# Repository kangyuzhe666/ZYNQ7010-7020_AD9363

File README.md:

# ZYNQ7010/7020_AD9363/AD9364/AD9361

####  Open source SDR hardware based on ZYNQ+AD936X

[中文](./README_CN.md) 
##  Open source SDR hardware based on ZYNQ+AD936X

## The preliminary development work has been completed and the product has entered the trial production stage. Please contact the email address: 1399109998@qq.com for finished products.
2022-09-13 update

## formal support openwifi

openwifi test video
- https://www.bilibili.com/video/BV1hB4y1k7dm?spm_id_from=333.999.list.card_archive.click

Project introduction video:

- https://www.youtube.com/watch?v=Qk-M8yRsKvs 

- https://www.youtube.com/watch?v=xx4MXQSHmCM&t=153s

GSM signals receiver test:
- https://www.youtube.com/watch?v=yFEpSrWW0-w

FM signal receiver test:
- https://www.youtube.com/watch?v=ASb7dLIEmfY

Sine wave signal transmission test:
- https://www.youtube.com/watch?v=bfs_GfULIoA&t=55s

Loopback signal test:
- https://www.youtube.com/watch?v=JOjsKboq0xA

The pluto-sdr firmware transplantation work is all done, flashing the firmware without hacking the system, the default is AD9364.

#### 1. Hardware solution

FPGA: ZYNQ7010/7020 (ZYNQ7010 and ZYNQ7020 can be replaced with each other, if you need more hardware resources, please use ZYNQ7020)

RF: AD9361/AD9363/AD9364 (the three chips can be replaced with each other, the difference lies in the bandwidth. Among them, AD9361 has better performance, try to use the ABCZ ending chip, which is different from BBCZ)

https://ez.analog.com/wide-band-rf-transceivers/design-support/f/q-a/80027/what-is-difference-of-ad9363-abcz-and-bbcz?ReplyOffsetId=179002&ReplyOffsetDirection=Next&ReplySortBy=CreatedDate&ReplySortOrder=Ascending&pifragment-7309=2

AD9363ABCZ Band: 325 MHz to 3.8 GHz

AD9363BBCZ Band: 650 MHz to 2.7 GHz

RAM Memory: DDR3 256M16

USB-PHY: USB3320C

GMAC-PHY: RTL8211E-VL (RTL8211E has two endings, VB and VL, where VB level is 3.3V/2.5V, VL is 1.8V)

QSPI FLASH: W25Q256 32MB

Power supply topology diagram

block design

##### 2. Software resources

Support Pluto-SDR firmware transplantation, OpenWiFi (ZYNQ7020 FPGA required), support adi official ZED+AD-FMCOMMS2/3/4 related firmware code

#### 3. PCB board design

Design software:  Altium Designer Kicad

Number of layers: 4 layers （signal layer[1]、GND[2]、POWER[3]、signal layer[4]）

Craft: JLC PCB Craft

Impedance: not supported

The impedance version will be tested in March 2021, and the openwifi port is currently undergoing normal transceiver tests.

#### 4. Differences compared to ADALM-PLUTO:

- Support for Zynq-7020 and Zynq-7010 in 400pin BGA package
- Support 2R2T transceiver mode
- 4 layer board to reduce cost
- SD slot for running real Linux distros
- Support Gigabit Ethernet

#### 5. Project display:

This is the PCB rendering

This is the physical picture of the PCB

This is the details of the PCB RF part

Ethernet can work stably at 1000M (using single-arm routing for testing in the figure)

AD9363 initializes the normal graph using adi no-os test environment

Pluto-uboot transplanted successfully

Pluto firmware works fine

Receive GSM signal normally

Hack into AD9364 to receive FM signal

Two PCBAs receive and send each other test

PCBAs can be stacked on each other and connected through Gigabit switches and routers

Support SDR-SHARP

##### 6.TO DO LIST

- Continue to optimize the RF part to reach the adi official demo board indicators
- Impedance design based on four-layer pcb
- To be completed in January-February of 2021, to complete the relevant transplantation work of openwifi
- Design the impedance version in March 2021
- Conduct commercial index tests on the impedance version in April 2021
- When the commercial version is launched at the end of April 2021, it will support adi's official SDR firmware (ADRV9364 packet), openwifi, and openbts openbts, etc.

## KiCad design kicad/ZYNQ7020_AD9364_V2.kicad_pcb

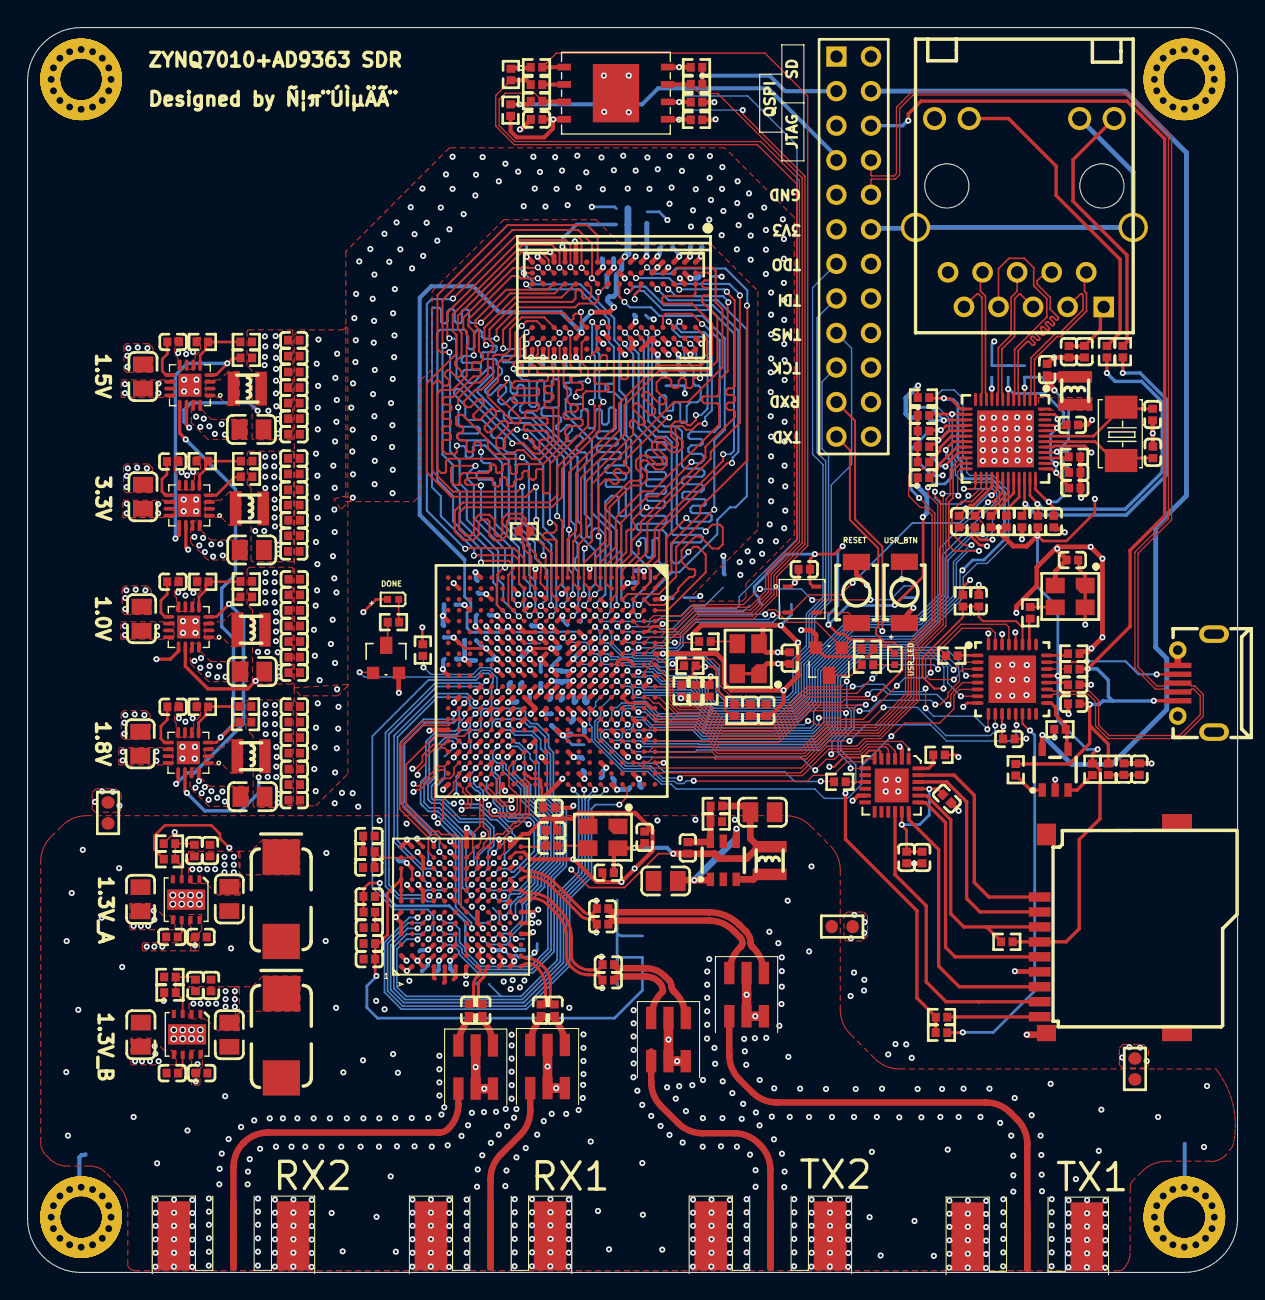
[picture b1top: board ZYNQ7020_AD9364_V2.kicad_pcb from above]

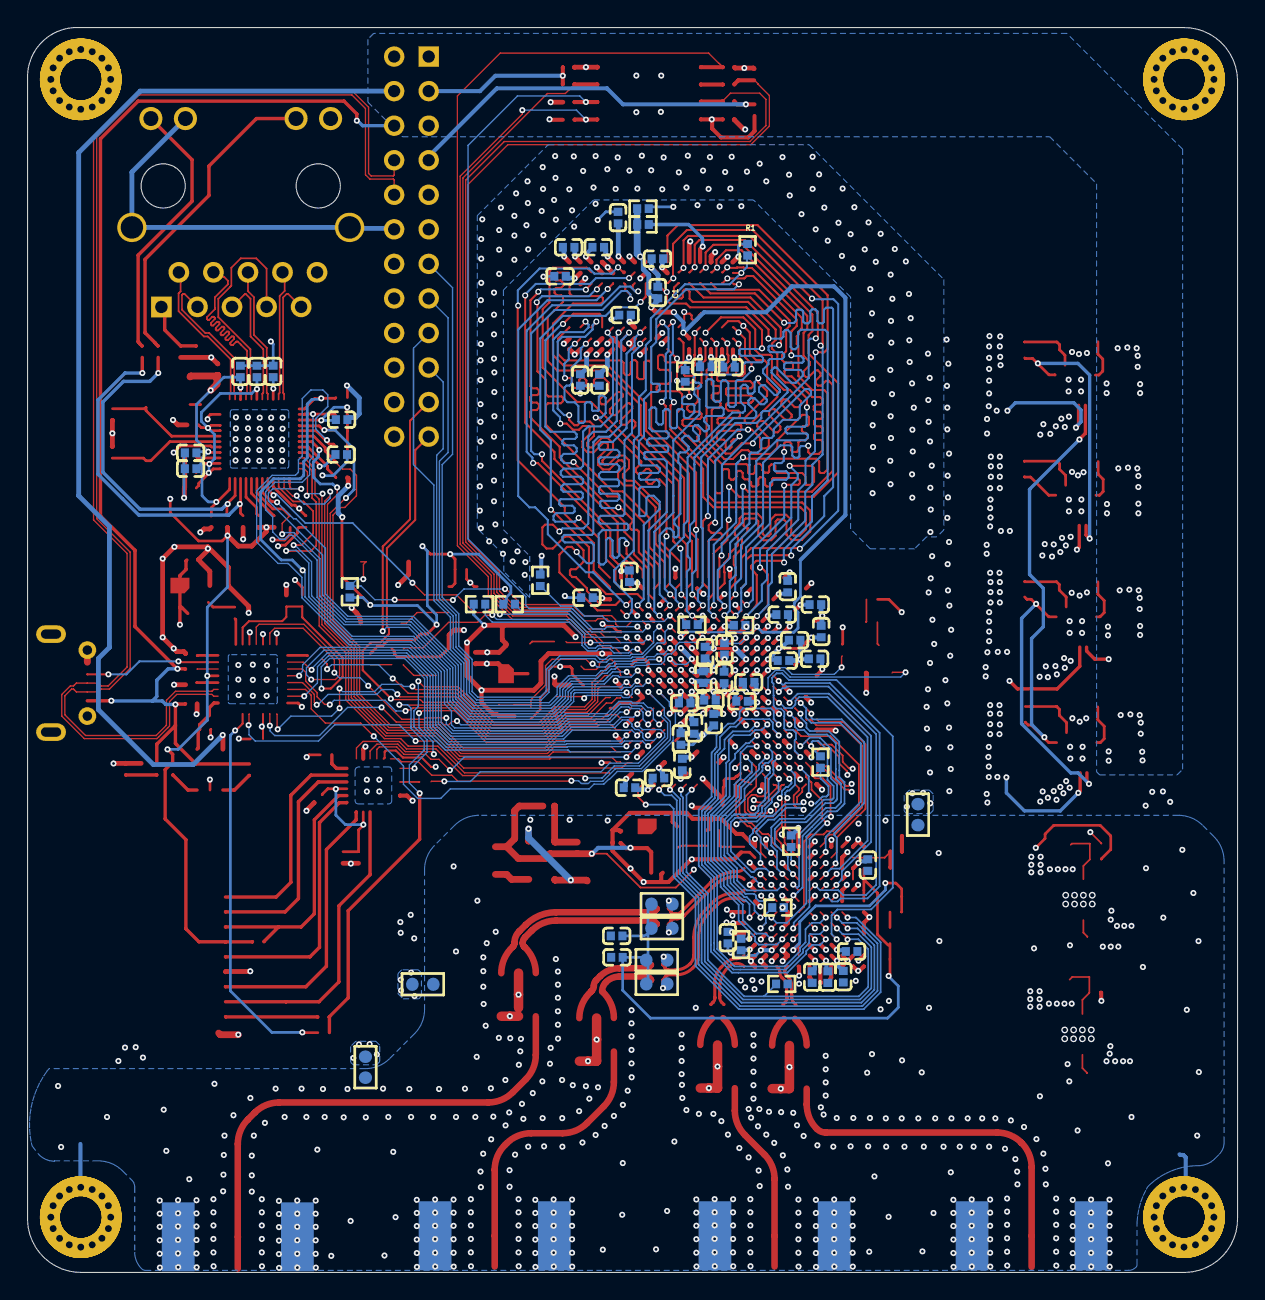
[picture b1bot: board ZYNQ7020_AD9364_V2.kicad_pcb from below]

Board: 4 copper layers, 89.0 x 91.5 mm, 287 parts (71 on the bottom side), 278 nets.

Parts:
*: W25Q128
C1, C159, C160, C161, C187, C188, C189, C190, C191, C192, C193: 104; CAP
C2, C3, C4, C5, C8, C9, C10, C12, C33, C34, C35, C36, C37, C38, C39, C49, C50, C51, C52, C53, C57, C61, C62, C67, C68, C69, C70, C71, C72, C73, C74, C75, C76, C77, C78, C80, C81, C82, C83, C85, C86, C87, C89, C90, C91, C96, C98, C99, C100, C101, C102, C103, C104, C105, C106, C107, C108, C148, C149, C181, C182, C183: 10¦ÌF; CAP_3
C6, C7, C11, C13, C18, C21, C23, C26, C27, C28: 0.1¦ÌF; CAP_3
C16, C29, C30, C31, C32, C40, C47, C48, C117, C118, C150, C152: 18p; CAP_1
C17, C20, C22, C25: 2.2¦ÌF; CAP_3
C19, C24: 3.3nF; CAP_3
C58, C60, C121, C139, C144: 10¦Ì; CAP_2
C59, C63: 0.001¦Ì; CAP_2
C109, C110, C111, C113, C114, C115, C116, C124, C125, C126, C127, C128, C130, C131, C142: 1¦Ì; CAP_2
C112, C120, C122, C132, C133, C134, C138, C141, C143: 0.1¦Ì; CAP_2
C119: 0.01¦Ì; CAP_2
C129, C135, C136, C137: 4.7¦Ì; CAP_2
C145, C166, C170, C172, C174: 1¦Ì; CAP_1
C146, C151, C175, C177: 0.001¦Ì; CAP_1
CP1, CP3: 22uF; CAP_1
CP2: 22pF; CAP_2
Ct1, Ct2: 3.3nF; CAP_3_3
DONE: LED; LED0
J2: microusb
L1, L2, L3, L4, L6: 2.2uH; INDUCTANCE_1
L5, L7, L8, L9: 330nh; INDUCTANCE
LG1: HR911130C
LP1: 4.7uH; INDUCTANCE
P2: Header 12X2A
Q1, Q2: AO3400
R1, R4, R5, R27, R35, R36, R38, R39, R40, R41, R43, R45, R46, R55, R57, R62, R63: 4.7K; RES
R2, R3: 82R; RES
R6: 240R; RES
R7, R68: 100K; RES
R8, R13, R15, R19, R24, R25, R30, R54, R65, R69, R71: 10K; RES
R9: 4.99K; RES
R10: 18.7K; RES
R11, R47, R49, R50, R51, R52, R53, R56: 20K; RES
R12, R17: 15K; RES
R14: 13K; RES
R16: 56.2K; RES
R18: 18K; RES
R20: 80.6R; RES
R21, R22: 6.25K; RES
R23, R64, R67: 0R; RES
R26: 2.49K; RES
R28, R29, R37, R42, R58, R76: 33R; RES
R31, R32, R70: 330R; RES
R33, R34: 1.5K; RES
R44: 8.06K; RES
R48, R66: 1K; RES
R59, R60, R61: 470R; RES
R72: 40.2R; RES
R73, R74: 1R; RES_1
R75: 14.3K; RES_1
RESET: SW-PB
RP1: 10K; RES_1
RP2: 20K; RES_1
RX1, RX2: JCCEM001
RX4, RX5, RX6, RX7, RX8, RX10, RX13, RX14, RX15, RX22: 0R; RES_1
T1, T2, T3, T4: TCM1-63AX+
TU1: TPS2051BDBVR
TX1, TX2: JCCEM001
U1: XC7Z010-CLG400
U2: MT41J64M16JT-187EG; DDR3
U3: RTL8211E-VB-CG
U4: USB3320C
U5: AD9363
U6, U7, U8, U9: TLV62130
U11, U12: TPS7A8101
U13: TCM811TE
UP1: AP3419
USD1: TXS02612RTWR
USR_BTN: SW-PB
USR_LED: LED; LED0
X1: 25M; XTAL-2
X2: 33.333MHz; XTAL-4
X3: 24MHz; XTAL-4
X4: 40MHz; XTAL-4
tf1: TF-SD

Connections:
1P3_TX: C58.1, C59.2, C60.1, C63.2, L5.1, L7.1, L8.1, L9.1, U5.A7, U5.A8, U5.A9, U5.A10
AD9361_CLKOUT: U1.W18, U5.J6
AD9361_RST: RX4.1, U1.R19, U5.K5
ADVDD10: C124.1, C125.1, C126.1, C127.2, C128.2, C130.2, C131.2, L6.2, U3.3, U3.9, U3.28, U3.36, U3.40
CB: *.6, R58.1
CTRL_IN0: U1.G20, U5.C5
CTRL_IN1: U1.D20, U5.C6
CTRL_IN2: U1.F20, U5.D6
CTRL_IN3: U1.H20, U5.D5
CTRL_OUT0: U1.V17, U5.D4
CTRL_OUT1: U1.T14, U5.E4
CTRL_OUT2: U1.T15, U5.E5
CTRL_OUT3: U1.P14, U5.E6
CTRL_OUT4: U1.U14, U5.F6
CTRL_OUT5: U1.U15, U5.F5
CTRL_OUT6: U1.T19, U5.F4
CTRL_OUT7: U1.V18, U5.G4
DATA_CLK_N: U1.U19, U5.H11
DATA_CLK_P: U1.U18, U5.G11
DDR3_A0: U1.N2, U2.N3
DDR3_A1: U1.K2, U2.P7
DDR3_A2: U1.M3, U2.P3
DDR3_A3: U1.K3, U2.N2
DDR3_A4: U1.M4, U2.P8
DDR3_A5: U1.L1, U2.P2
DDR3_A6: U1.L4, U2.R8
DDR3_A7: U1.K4, U2.R2
DDR3_A8: U1.K1, U2.T8
DDR3_A9: U1.J4, U2.R3
DDR3_A10: U1.F5, U2.L7
DDR3_A11: U1.G4, U2.R7
DDR3_A12: U1.E4, U2.N7
DDR3_A13: U1.D4, U2.T3
DDR3_A14: U1.F4, U2.T7
DDR3_BA0: U1.L5, U2.M2
DDR3_BA1: U1.R4, U2.N8
DDR3_BA2: U1.J5, U2.M3
DDR3_CAS: U1.P5, U2.K3
DDR3_CKE: U1.N3, U2.K9
DDR3_CK_N: R20.2, U1.M2, U2.K7
DDR3_CK_P: R20.1, U1.L2, U2.J7
DDR3_CS: U1.N1, U2.L2
DDR3_DM0: U1.A1, U2.E7
DDR3_DM1: U1.F1, U2.D3
DDR3_DQ0: U1.C3, U2.E3
DDR3_DQ1: U1.B3, U2.F7
DDR3_DQ2: U1.A2, U2.F2
DDR3_DQ3: U1.A4, U2.F8
DDR3_DQ4: U1.D3, U2.H3
DDR3_DQ5: U1.D1, U2.H8
DDR3_DQ6: U1.C1, U2.G2
DDR3_DQ7: U1.E1, U2.H7
DDR3_DQ8: U1.E2, U2.D7
DDR3_DQ9: U1.E3, U2.C3
DDR3_DQ10: U1.G3, U2.C8
DDR3_DQ11: U1.H3, U2.C2
DDR3_DQ12: U1.J3, U2.A7
DDR3_DQ13: U1.H2, U2.A2
DDR3_DQ14: U1.H1, U2.B8
DDR3_DQ15: U1.J1, U2.A3
DDR3_DQS0_N: U1.B2, U2.G3
DDR3_DQS0_P: U1.C2, U2.F3
DDR3_DQS1_N: U1.F2, U2.B7
DDR3_DQS1_P: U1.G2, U2.C7
DDR3_ODT: U1.N5, U2.K1
DDR3_RAS: U1.P4, U2.J3
DDR3_RESET: R1.1, U1.B4, U2.T2
DDR3_VREF: C1.1, R4.1, R5.2, U1.H6, U1.P6, U2.H1, U2.M8
DDR3_WE: U1.M5, U2.L3
ENABLE: U1.V15, U5.G6
EN_AGC: U1.W19, U5.G5
ETH_MDC: U1.C10, U3.30
ETH_MDIO: R34.2, U1.C11, U3.31
ETH_RXCK: U1.B17, U3.19
ETH_RXCTL: R36.2, U1.D13, U3.13
ETH_RXD0: R41.1, U1.D11, U3.14
ETH_RXD1: R39.1, U1.A16, U3.16
ETH_RXD2: R43.1, U1.F15, U3.17
ETH_RXD3: R45.1, U1.A15, U3.18
ETH_TXCK: U1.A19, U3.22
ETH_TXCTL: U1.F14, U3.27
ETH_TXD0: U1.E14, U3.23
ETH_TXD1: U1.B18, U3.24
ETH_TXD2: U1.D10, U3.25
ETH_TXD3: U1.A17, U3.26
FB_CLK_N: RX22.2, U1.U17, U5.G10
FB_CLK_P: U1.T16, U5.F10
FPGA_DONE: Q1.1, U1.R11
FPGA_TCK: P2.10, U1.F9
FPGA_TDI: P2.8, U1.G6
FPGA_TDO: P2.7, U1.F6
FPGA_TMS: P2.9, U1.J6
GND: *.4, C1.2, C2.1, C3.1, C4.1, C5.1, C6.1, C7.1, C8.1, C9.1, C10.1, C11.1, C12.1, C13.1, C33.1, C34.1, C35.1, C36.1, C37.1, C38.1, C39.1, C49.1, C50.1, C51.1, C52.1, C53.1, C57.1, C61.1, C62.1, C67.1, C68.1, C69.1, C70.1, C71.1, C72.1, C73.1, C74.1, C75.1, C76.1, C77.1, C78.1, C80.1, C81.2, C82.1, C83.1, C85.1, C86.1, C87.1, C89.1, C90.1, C91.1, C96.1, C98.2, C99.2, C100.2, C101.2, C102.2, C103.2, C104.2, C105.2, C106.2, C107.2, C108.2, C109.1, C110.1, C111.2, C112.2, C113.1, C114.1, C115.1, C116.1, C117.2, C118.2, C119.1, C120.2, C121.1, C122.2, C124.2, C125.2, C126.2, C127.1, C128.1, C129.2, C130.1, C131.1, C132.2, C133.2, C134.2, C135.2, C136.2, C137.2, C138.2, C139.2, C141.2, C148.2, C149.2, C159.1, C160.1, C161.1, C181.2, C182.2, C183.2, C187.1, C188.1, C189.1, C190.1, C191.1, C192.1, C193.1, J2.5, J2.6, J2.7, J2.8, J2.9, LG1.12, LG1.P10, LG1.SHIELD0, LG1.SHIELD1, P2.3, P2.5, P2.18, P2.19, P2.20, P2.21, P2.22, P2.23, P2.24, Q1.2, Q2.2, R1.2, R2.1, R5.1, R6.2, R11.2, R12.2, R17.2, R18.2, R26.2, R28.2, R36.1, R40.1, R44.2, R49.1, R51.1, R53.1, R54.2, R56.1, R62.1, R65.2, R69.2, RESET.1, RX6.2, RX7.2, RX8.2, RX13.2, RX14.2, RX15.2, TU1.2, U1.A8, U1.A18, U1.B1, U1.B11, U1.C4, U1.C9, U1.C14, U1.D17, U1.E10, U1.E20, U1.F3, U1.F7, U1.F10, U1.G10, U1.G12, U1.G16, U1.H7, U1.H9, U1.H11, U1.H13, U1.H19, U1.J2, U1.J8, U1.J10, U1.J12, U1.K5, U1.K7, U1.K10, U1.K11, U1.K13, U1.K15, U1.L8, U1.L9, U1.L12, U1.L18, U1.M1, U1.M7, U1.M9, U1.M10, U1.M11, U1.M13, U1.N4, U1.N8, U1.N10, U1.N12, U1.N14, U1.P7, U1.P9, U1.P11, U1.P13, U1.P17, U1.R8, U1.R12, U1.R20, U1.T3, U1.T7, U1.T13, U1.U6, U1.U16, U1.V9, U1.V19, U1.W2, U1.W12, U1.Y5, U1.Y15, U2.A9, U2.B1, U2.B3, U2.B9, U2.D1, U2.D8, U2.E1, U2.E2, U2.E8, U2.F9, U2.G1, U2.G8, U2.G9, U2.J2, U2.J8, U2.M1, U2.M9, U2.P1, U2.P9, U2.T1, U2.T9, U3.0, U3.47, U4.0, U6.6, U6.7, U6.8, U6.15, U6.16, U6.20, U7.6, U7.7, U7.8, U7.15, U7.16, U7.20, U8.6, U8.7, U8.8, U8.15, U8.16, U8.20, U9.6, U9.7, U9.8, U9.15, U9.16, U9.20, U13.1, USD1.2, USD1.11, USD1.25, USR_BTN.1, X2.2, X3.2, tf1.6, tf1.10
NetC6_2: C6.2, U6.9
NetC7_2: C7.2, U7.9
NetC11_2: C11.2, U8.9
NetC13_2: C13.2, U9.9
NetC19_1: C19.1, R21.2, R24.1, U11.3
NetC24_1: C24.1, R22.2, R25.1, U12.3
NetC27_2: C27.2, U11.6
NetC28_2: C28.2, U12.6
NetC111_1: C111.1, C112.1, LG1.P1
NetC117_1: C117.1, U3.43, X1.1
NetC118_1: C118.1, U3.42, X1.2
NetC119_2: C119.2, R28.1, R29.1, U1.E11
NetC129_1: C129.1, U4.20
NetC135_1: C135.1, C136.1, R64.1
NetC142_1: C142.1, R73.2
NetC145_2: C145.2, R74.1
NetC146_2: C146.2, R73.1, U5.G2, U5.G3
NetC148_1: C148.1, C149.1, R23.2, U1.G8
NetC150_2: C150.2, C152.1, U5.M12
NetC151_2: C151.2, R74.2, U5.A11, U5.B11
NetC152_2: C152.2, X4.3
NetCP2_2: CP2.2, RP1.1, RP2.2, UP1.6
NetDONE_2: DONE.2, R61.2
NetL1_1: L1.1, U6.1, U6.2, U6.3
NetL2_1: L2.1, U7.1, U7.2, U7.3
NetL3_1: L3.1, U8.1, U8.2, U8.3
NetL4_1: L4.1, U9.1, U9.2, U9.3
NetLG1_11: LG1.11, R32.2
NetLG1_13: LG1.13, R31.2
NetLP1_1: LP1.1, UP1.3
NetP2_2: P2.2, R52.1, R54.1
NetP2_4: P2.4, R48.2, R50.1
NetQ1_3: Q1.3, R61.1
NetQ2_3: Q2.3, R60.1
NetR2_2: R2.2, U1.H5
NetR3_2: R3.2, U1.G5
NetR6_1: R6.1, U2.L8
NetR9_2: R9.2, R11.1, U6.5
NetR10_2: R10.2, R12.1, U7.5
NetR14_2: R14.2, R17.1, U8.5
NetR15_2: R15.2, U9.4
NetR16_2: R16.2, R18.1, U9.5
NetR26_1: R26.1, U3.39
NetR27_1: R27.1, U3.32
NetR30_2: R30.2, U1.B10
NetR37_2: R37.2, X2.3
NetR38_2: R38.2, U3.20
NetR42_2: R42.2, U4.1
NetR44_1: R44.1, U4.24
NetR55_2: R55.2, U1.R10
NetR57_2: R57.2, U1.L6
NetR60_2: R60.2, USR_LED.2
NetR62_2: R62.2, USD1.24
NetR63_2: R63.2, USD1.20, tf1.3
NetR67_2: R67.2, TU1.1
NetR68_1: R68.1, TU1.3
NetR70_1: R70.1, tf1.9
NetR72_1: R72.1, USD1.9
NetR75_1: R75.1, U5.L4
NetR76_2: R76.2, X3.3
NetRESET_2: RESET.2, U13.3
NetRX1_1: RX1.1, T1.3
NetRX2_1: RX2.1, T2.3
NetT3_3: T3.3, TX1.1
NetT4_3: T4.3, TX2.1
Nettf1_1: USD1.23, tf1.1
Nettf1_2: USD1.22, tf1.2
Nettf1_5: USD1.19, tf1.5
Nettf1_7: USD1.18, tf1.7
Nettf1_8: USD1.16, tf1.8
OTG_CLK: R42.1, U1.A11
OTG_DATA0: U1.A14, U4.3
OTG_DATA1: U1.D15, U4.4
OTG_DATA2: U1.A12, U4.5
OTG_DATA3: U1.F12, U4.6
OTG_DATA4: U1.C16, U4.7
OTG_DATA5: U1.A10, U4.9
OTG_DATA6: U1.E13, U4.10
OTG_DATA7: U1.C18, U4.13
OTG_DIR: U1.C13, U4.31
OTG_NXT: U1.E16, U4.2
OTG_RESETN: C121.2, R33.1, U1.D16, U4.27
OTG_STP: U1.C15, U4.29
PG_1V0: R7.2, U6.4, U7.13
PG_1V5: R13.2, U8.4, U9.13
PG_1V8: R8.2, U7.4, U8.13
PHY_AD0/LED0: R31.1, R46.2, U3.35
PHY_AD1/LED1: R32.1, R40.2, U3.34
PHY_MDI0_N: LG1.P3, U3.2
PHY_MDI0_P: LG1.P2, U3.1
PHY_MDI1_N: LG1.P7, U3.5
PHY_MDI1_P: LG1.P4, U3.4
PHY_MDI2_N: LG1.P6, U3.8
PHY_MDI2_P: LG1.P5, U3.7
PHY_MDI3_N: LG1.P9, U3.11
PHY_MDI3_P: LG1.P8, U3.10
PMEB: R35.2, U3.33
PS_CLK_500: R37.1, U1.E7
PS_MIO7: R56.2, U1.D8
PS_MIO8: R47.2, U1.D5
PS_PRO_B: U1.C7, U3.29, U13.2
QSPI_CS: *.1, R59.1, U1.A7
QSPI_D0: *.5, R49.2, U1.B8
QSPI_D1: *.2, R51.2, U1.D6
QSPI_D2: *.3, R52.2, U1.B7
QSPI_D3: *.7, R50.2, U1.A6
QSPI_SCK: R53.2, R58.2, U1.A5
REG_OUT: L6.1, U3.48
RFGND: C17.1, C18.1, C20.1, C21.1, C22.1, C23.1, C25.1, C26.1, C27.1, C28.1, C58.2, C59.1, C60.2, C63.1, C142.2, C143.1, C144.1, C145.1, C146.1, C150.1, C151.1, C166.2, C170.2, C172.2, C174.2, C175.2, C177.2, CP1.1, CP3.1, Ct1.2, Ct2.2, R24.2, R25.2, R75.2, RP1.2, RX1.2, RX1.3, RX1.4, RX1.5, RX2.2, RX2.3, RX2.4, RX2.5, RX5.1, RX6.1, RX7.1, RX8.1, RX10.1, RX13.1, RX14.1, RX15.1, RX22.1, T1.1, T1.2, T1.5, T2.1, T2.2, T2.5, T3.1, T3.2, T3.5, T4.1, T4.2, T4.5, TX1.2, TX1.3, TX1.4, TX1.5, TX2.2, TX2.3, TX2.4, TX2.5, U5.A1, U5.A2, U5.A4, U5.A5, U5.A6, U5.A12, U5.B1, U5.B2, U5.B12, U5.C1, U5.C2, U5.C7, U5.C8, U5.C9, U5.C10, U5.C11, U5.C12, U5.D1, U5.D12, U5.E1, U5.F1, U5.F3, U5.F7, U5.F9, U5.F11, U5.G1, U5.G12, U5.H2, U5.H3, U5.H5, U5.H6, U5.H7, U5.H10, U5.J2, U5.K1, U5.K2, U5.K12, U5.L1, U5.L2, U5.L3, U5.L7, U5.L8, U5.L9, U5.L10, U5.L11, U5.L12, U5.M4, U5.M5, U5.M6, U11.0, U11.4, U12.0, U12.4, UP1.2, X4.2
RX1AN_N: C16.1, T1.6
RX1AN_P: C30.1, T1.4
RX1A_N: C16.2, U5.M2
RX1A_P: C30.2, U5.M1
RX1BN_N: C29.1, T2.6
RX1BN_P: C31.1, T2.4
RX1B_N: C29.2, U5.J1
RX1B_P: C31.2, U5.H1
RX_D0_N: U1.P20, U5.K11
RX_D0_P: U1.N20, U5.J12
RX_D1_N: U1.W20, U5.K10
RX_D1_P: U1.V20, U5.J11
RX_D2_N: U1.U20, U5.K9
RX_D2_P: U1.T20, U5.J10
RX_D3_N: U1.R18, U5.K8
RX_D3_P: U1.T17, U5.J9
RX_D4_N: U1.P19, U5.K7
RX_D4_P: U1.N18, U5.J8
RX_D5_N: U1.R17, U5.J7
RX_D5_P: U1.R16, U5.H8
RX_FRAME_N: U1.V13, U5.G7
RX_FRAME_P: U1.U13, U5.G8
SD_CD: R70.2, R71.1, U1.B14
SD_CLK: R72.2, U1.D14
SD_CMD: U1.C17, USD1.4
SD_D0: U1.E12, USD1.6
SD_D1: U1.A9, USD1.7
SD_D2: U1.F13, USD1.1
SD_D3: U1.B15, USD1.3
SPI_CLK: U1.P18, U5.J5
SPI_DI: U1.P15, U5.J4
SPI_DO: U1.P16, U5.L6
SPI_ENB: U1.N17, U5.K6
TEST/ENABLE: RX5.2, U1.J20, U5.C4
TX1AN_N: C48.2, T4.6
TX1AN_P: C40.2, T4.4
TX1A_N: C48.1, L9.2, U5.M8
TX1A_P: C40.1, L8.2, U5.M7
TX1BN_N: C47.2, T3.6
TX1BN_P: C32.2, T3.4
TX1B_N: C47.1, L7.2, U5.M10
TX1B_P: C32.1, L5.2, U5.M9
TXNRX: U1.R14, U5.H4
TX_D0_N: U1.T10, U5.E7
TX_D0_P: U1.T11, U5.F8
TX_D1_N: U1.Y17, U5.D7
TX_D1_P: U1.Y16, U5.E8
TX_D2_N: U1.U12, U5.D8
TX_D2_P: U1.T12, U5.E9
TX_D3_N: U1.Y19, U5.D9
TX_D3_P: U1.Y18, U5.E10
TX_D4_N: U1.W13, U5.D10
TX_D4_P: U1.V12, U5.E11
TX_D5_N: U1.Y14, U5.D11
TX_D5_P: U1.W14, U5.E12
TX_FRAME_N: RX10.2, U1.W16, U5.H9
TX_FRAME_P: U1.V16, U5.G9
UART_RX: P2.11, U1.C12
UART_TX: P2.12, U1.B12
USB2_5V: C137.1, J2.1, P2.15, R64.2, R66.1, R67.1
USB3320_CLK: R76.1, U4.26
USB_ID: J2.4, U4.23
USB_OTG_N: J2.2, P2.17, U4.19
USB_OTG_P: J2.3, P2.16, U4.18
USB_VBUS: R66.2, U4.22
USR_BTN: R19.2, U1.C5, USR_BTN.2
USR_LED: Q2.1, R65.1, U1.C8
VCC1P8: C143.2, C144.2, CP2.1, CP3.2, LP1.2, RP2.1, U5.H12, X4.4
VCC_1V0: C2.2, C33.2, C34.2, C35.2, C36.2, C37.2, C38.2, C39.2, C49.2, C50.2, C51.2, C52.2, C53.2, C57.2, C67.2, L1.2, R7.1, R9.1, U1.G7, U1.G11, U1.G13, U1.H10, U1.H12, U1.J7, U1.J13, U1.K12, U1.L7, U1.L13, U1.M12, U1.N7, U1.N13, U1.P8, U1.P12, U1.R7, U1.R13, U6.14
VCC_1V5: C8.2, C81.1, C98.1, C99.1, C100.1, C101.1, C102.1, C103.1, C104.1, C105.1, C106.1, C107.1, C108.1, C159.2, C160.2, C161.2, C187.2, C188.2, C189.2, C190.2, C191.2, C192.2, C193.2, L3.2, R3.1, R4.2, R13.1, R14.1, U1.A3, U1.D2, U1.E5, U1.G1, U1.H4, U1.L3, U1.P2, U1.R5, U1.U1, U1.V4, U2.A1, U2.A8, U2.B2, U2.C1, U2.C9, U2.D2, U2.D9, U2.E9, U2.F1, U2.G7, U2.H2, U2.H9, U2.K2, U2.K8, U2.N1, U2.N9, U2.R1, U2.R9, U8.14
VCC_1V8: C3.2, C61.2, C62.2, C68.2, C69.2, C70.2, C71.2, C72.2, C73.2, C74.2, C80.2, C82.2, C83.2, C85.2, C86.2, C87.2, C89.2, C90.2, C91.2, C96.2, C109.2, C110.2, C122.1, C141.1, L2.2, R8.1, R10.1, R23.1, R29.2, R30.1, R33.2, R34.1, R39.2, R41.2, R43.2, R45.2, R71.2, U1.A13, U1.B16, U1.C19, U1.D12, U1.E15, U1.F8, U1.F11, U1.F18, U1.G9, U1.H8, U1.H14, U1.J9, U1.J11, U1.J17, U1.K8, U1.K20, U1.L11, U1.M8, U1.M16, U1.N9, U1.N11, U1.N19, U1.P10, U1.R9, U1.R15, U1.T8, U1.T18, U1.U11, U1.V14, U1.W7, U1.W17, U1.Y10, U1.Y20, U3.15, U3.21, U4.8, U4.11, U4.14, U4.28, U4.30, U4.32, U7.14, USD1.5, X3.1, X3.4
VCC_3V3: *.8, C9.2, C20.2, C21.2, C25.2, C26.2, C75.2, C76.2, C77.2, C78.2, C113.2, C114.2, C115.2, C116.2, C120.1, C132.1, C133.1, C134.1, C138.1, C139.1, C181.1, C182.1, C183.1, CP1.2, DONE.1, L4.2, LG1.14, P2.1, P2.6, R15.1, R16.1, R19.1, R27.2, R35.1, R38.1, R46.1, R47.1, R48.1, R55.1, R57.1, R59.2, R63.1, R68.2, U1.B6, U1.D7, U1.K6, U1.M6, U1.N6, U1.R6, U1.T6, U3.6, U3.37, U3.38, U3.41, U3.44, U3.45, U4.21, U9.14, U11.5, U11.7, U11.8, U12.5, U12.7, U12.8, U13.4, UP1.1, UP1.4, USD1.17, USD1.21, USR_LED.1, X2.1, X2.4, tf1.4
VCC_IN: C4.2, C5.2, C10.2, C12.2, P2.13, P2.14, TU1.5, U6.10, U6.11, U6.12, U6.13, U7.10, U7.11, U7.12, U8.10, U8.11, U8.12, U9.10, U9.11, U9.12
VDDA_RX_LO: C17.2, C18.2, C19.2, C166.1, C170.1, C174.1, C175.1, Ct1.1, R21.1, U5.B9, U5.B10, U5.E2, U5.F2, U5.J3, U5.K3, U11.1, U11.2
VDD_DIG: C22.2, C23.2, C24.2, C172.1, C177.1, Ct2.1, R22.1, RX4.2, U5.B8, U5.D2, U5.D3, U5.E3, U5.F12, U5.K4, U12.1, U12.2
VUSB_V_EN: R69.1, TU1.4, U4.17

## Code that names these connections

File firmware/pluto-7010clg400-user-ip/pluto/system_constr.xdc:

# constraints
# ad9361 (SWAP == 0x1)

set_property  -dict {PACKAGE_PIN  U18  IOSTANDARD LVCMOS18 } [get_ports rx_clk_in]
set_property  -dict {PACKAGE_PIN  U13  IOSTANDARD LVCMOS18 } [get_ports rx_frame_in]
set_property  -dict {PACKAGE_PIN  P20  IOSTANDARD LVCMOS18 } [get_ports rx_data_in[0]]
set_property  -dict {PACKAGE_PIN  N20  IOSTANDARD LVCMOS18 } [get_ports rx_data_in[1]]
set_property  -dict {PACKAGE_PIN  W20  IOSTANDARD LVCMOS18 } [get_ports rx_data_in[2]]
set_property  -dict {PACKAGE_PIN  V20  IOSTANDARD LVCMOS18 } [get_ports rx_data_in[3]]
set_property  -dict {PACKAGE_PIN  U20  IOSTANDARD LVCMOS18 } [get_ports rx_data_in[4]]
set_property  -dict {PACKAGE_PIN  T20  IOSTANDARD LVCMOS18 } [get_ports rx_data_in[5]]
set_property  -dict {PACKAGE_PIN  R18  IOSTANDARD LVCMOS18 } [get_ports rx_data_in[6]]
set_property  -dict {PACKAGE_PIN  T17  IOSTANDARD LVCMOS18 } [get_ports rx_data_in[7]]
set_property  -dict {PACKAGE_PIN  P19  IOSTANDARD LVCMOS18 } [get_ports rx_data_in[8]]
set_property  -dict {PACKAGE_PIN  N18  IOSTANDARD LVCMOS18 } [get_ports rx_data_in[9]]
set_property  -dict {PACKAGE_PIN  R17  IOSTANDARD LVCMOS18 } [get_ports rx_data_in[10]]
set_property  -dict {PACKAGE_PIN  R16  IOSTANDARD LVCMOS18 } [get_ports rx_data_in[11]]

set_property  -dict {PACKAGE_PIN  T16  IOSTANDARD LVCMOS18} [get_ports tx_clk_out]
set_property  -dict {PACKAGE_PIN  V16  IOSTANDARD LVCMOS18} [get_ports tx_frame_out]
set_property  -dict {PACKAGE_PIN  W14  IOSTANDARD LVCMOS18} [get_ports tx_data_out[0]]
set_property  -dict {PACKAGE_PIN  Y14  IOSTANDARD LVCMOS18} [get_ports tx_data_out[1]]
set_property  -dict {PACKAGE_PIN  V12  IOSTANDARD LVCMOS18} [get_ports tx_data_out[2]]
set_property  -dict {PACKAGE_PIN  W13  IOSTANDARD LVCMOS18} [get_ports tx_data_out[3]]
set_property  -dict {PACKAGE_PIN  Y18  IOSTANDARD LVCMOS18} [get_ports tx_data_out[4]]
set_property  -dict {PACKAGE_PIN  Y19  IOSTANDARD LVCMOS18} [get_ports tx_data_out[5]]
set_property  -dict {PACKAGE_PIN  T12  IOSTANDARD LVCMOS18} [get_ports tx_data_out[6]]
set_property  -dict {PACKAGE_PIN  U12  IOSTANDARD LVCMOS18} [get_ports tx_data_out[7]]
set_property  -dict {PACKAGE_PIN  Y16  IOSTANDARD LVCMOS18} [get_ports tx_data_out[8]]
set_property  -dict {PACKAGE_PIN  Y17  IOSTANDARD LVCMOS18} [get_ports tx_data_out[9]]
set_property  -dict {PACKAGE_PIN  T11  IOSTANDARD LVCMOS18} [get_ports tx_data_out[10]]
set_property  -dict {PACKAGE_PIN  T10  IOSTANDARD LVCMOS18} [get_ports tx_data_out[11]]

set_property  -dict {PACKAGE_PIN  V17  IOSTANDARD LVCMOS18} [get_ports gpio_status[0]]
set_property  -dict {PACKAGE_PIN  T14  IOSTANDARD LVCMOS18} [get_ports gpio_status[1]]
set_property  -dict {PACKAGE_PIN  T15  IOSTANDARD LVCMOS18} [get_ports gpio_status[2]]
set_property  -dict {PACKAGE_PIN  P14  IOSTANDARD LVCMOS18} [get_ports gpio_status[3]]
set_property  -dict {PACKAGE_PIN  U14  IOSTANDARD LVCMOS18} [get_ports gpio_status[4]]
set_property  -dict {PACKAGE_PIN  U15  IOSTANDARD LVCMOS18} [get_ports gpio_status[5]]
set_property  -dict {PACKAGE_PIN  T19  IOSTANDARD LVCMOS18} [get_ports gpio_status[6]]
set_property  -dict {PACKAGE_PIN  V18  IOSTANDARD LVCMOS18} [get_ports gpio_status[7]]

set_property  -dict {PACKAGE_PIN  G20  IOSTANDARD LVCMOS18} [get_ports gpio_ctl[0]]
set_property  -dict {PACKAGE_PIN  D20  IOSTANDARD LVCMOS18} [get_ports gpio_ctl[1]]
set_property  -dict {PACKAGE_PIN  F20  IOSTANDARD LVCMOS18} [get_ports gpio_ctl[2]]
set_property  -dict {PACKAGE_PIN  H20  IOSTANDARD LVCMOS18} [get_ports gpio_ctl[3]]

set_property  -dict {PACKAGE_PIN  W19  IOSTANDARD LVCMOS18} [get_ports gpio_en_agc]
set_property  -dict {PACKAGE_PIN  R19  IOSTANDARD LVCMOS18} [get_ports gpio_resetb]

set_property  -dict {PACKAGE_PIN  V15  IOSTANDARD LVCMOS18} [get_ports enable]
set_property  -dict {PACKAGE_PIN  R14  IOSTANDARD LVCMOS18} [get_ports txnrx]

set_property  -dict {PACKAGE_PIN  J16  IOSTANDARD LVCMOS18 PULLTYPE PULLUP} [get_ports iic_scl]
set_property  -dict {PACKAGE_PIN  K16  IOSTANDARD LVCMOS18 PULLTYPE PULLUP} [get_ports iic_sda]

set_property  -dict {PACKAGE_PIN  N17  IOSTANDARD LVCMOS18  PULLTYPE PULLUP} [get_ports spi_csn]
set_property  -dict {PACKAGE_PIN  P18  IOSTANDARD LVCMOS18} [get_ports spi_clk]
set_property  -dict {PACKAGE_PIN  P15  IOSTANDARD LVCMOS18} [get_ports spi_mosi]
set_property  -dict {PACKAGE_PIN  P16  IOSTANDARD LVCMOS18} [get_ports spi_miso]

set_property  -dict {PACKAGE_PIN  L15  IOSTANDARD LVCMOS18} [get_ports gpio_bd]
set_property  -dict {PACKAGE_PIN  W18  IOSTANDARD LVCMOS18} [get_ports clk_out]

create_clock -name rx_clk -period  16.27 [get_ports rx_clk_in]

# probably gone in 2016.4

create_clock -name clk_fpga_0 -period 10 [get_pins "i_system_wrapper/system_i/sys_ps7/inst/PS7_i/FCLKCLK[0]"]
create_clock -name clk_fpga_1 -period  5 [get_pins "i_system_wrapper/system_i/sys_ps7/inst/PS7_i/FCLKCLK[1]"]

create_clock -name spi0_clk      -period 40   [get_pins -hier */EMIOSPI0SCLKO]

set_input_jitter clk_fpga_0 0.3
set_input_jitter clk_fpga_1 0.15



set_false_path -from [get_pins {i_system_wrapper/system_i/axi_ad9361/inst/i_rx/i_up_adc_common/up_adc_gpio_out_int_reg[0]/C}]
set_false_path -from [get_pins {i_system_wrapper/system_i/axi_ad9361/inst/i_tx/i_up_dac_common/up_dac_gpio_out_int_reg[0]/C}]

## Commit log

2020-11-10 第一次提交
    第一次提交
2020-11-10 修改了3.3V网络标号错误
    修改了3.3V网络标号错误，去掉一些退耦电容
2020-11-11 修改了射频覆铜
    修改了射频覆铜
2020-11-11 更新了README
    更新了README
2020-11-11 更新bom和阻值标注
2020-11-12 添加丝印和焊盘泪滴
2020-11-17 提交固件工程，重新设计文件目录
2020-11-17 sdk代码
2020-11-19 更新readme
2020-11-20 修改ddr连接
2020-11-20 修改射频部分
2020-11-30 修改lvds走线
2020-12-02 更新布线
2020-12-05 最新布线2r2t
2020-12-07 更新丝印
2020-12-07 更新 README
2020-12-07 后续修改
2020-12-07 更新固件
2020-12-12 删除错误图纸
2020-12-18 create document
2020-12-23 添加pluto-sdr二进制固件
2020-12-30 更新pcb设计
2021-01-03 kicad
2021-01-05 更新tcl脚本
2021-01-06 update firmware
2021-01-14 update firmware for ad9364
2021-01-14 update hardware
2021-01-18 required
2021-01-23 upadte readme
2022-09-13 readme update
